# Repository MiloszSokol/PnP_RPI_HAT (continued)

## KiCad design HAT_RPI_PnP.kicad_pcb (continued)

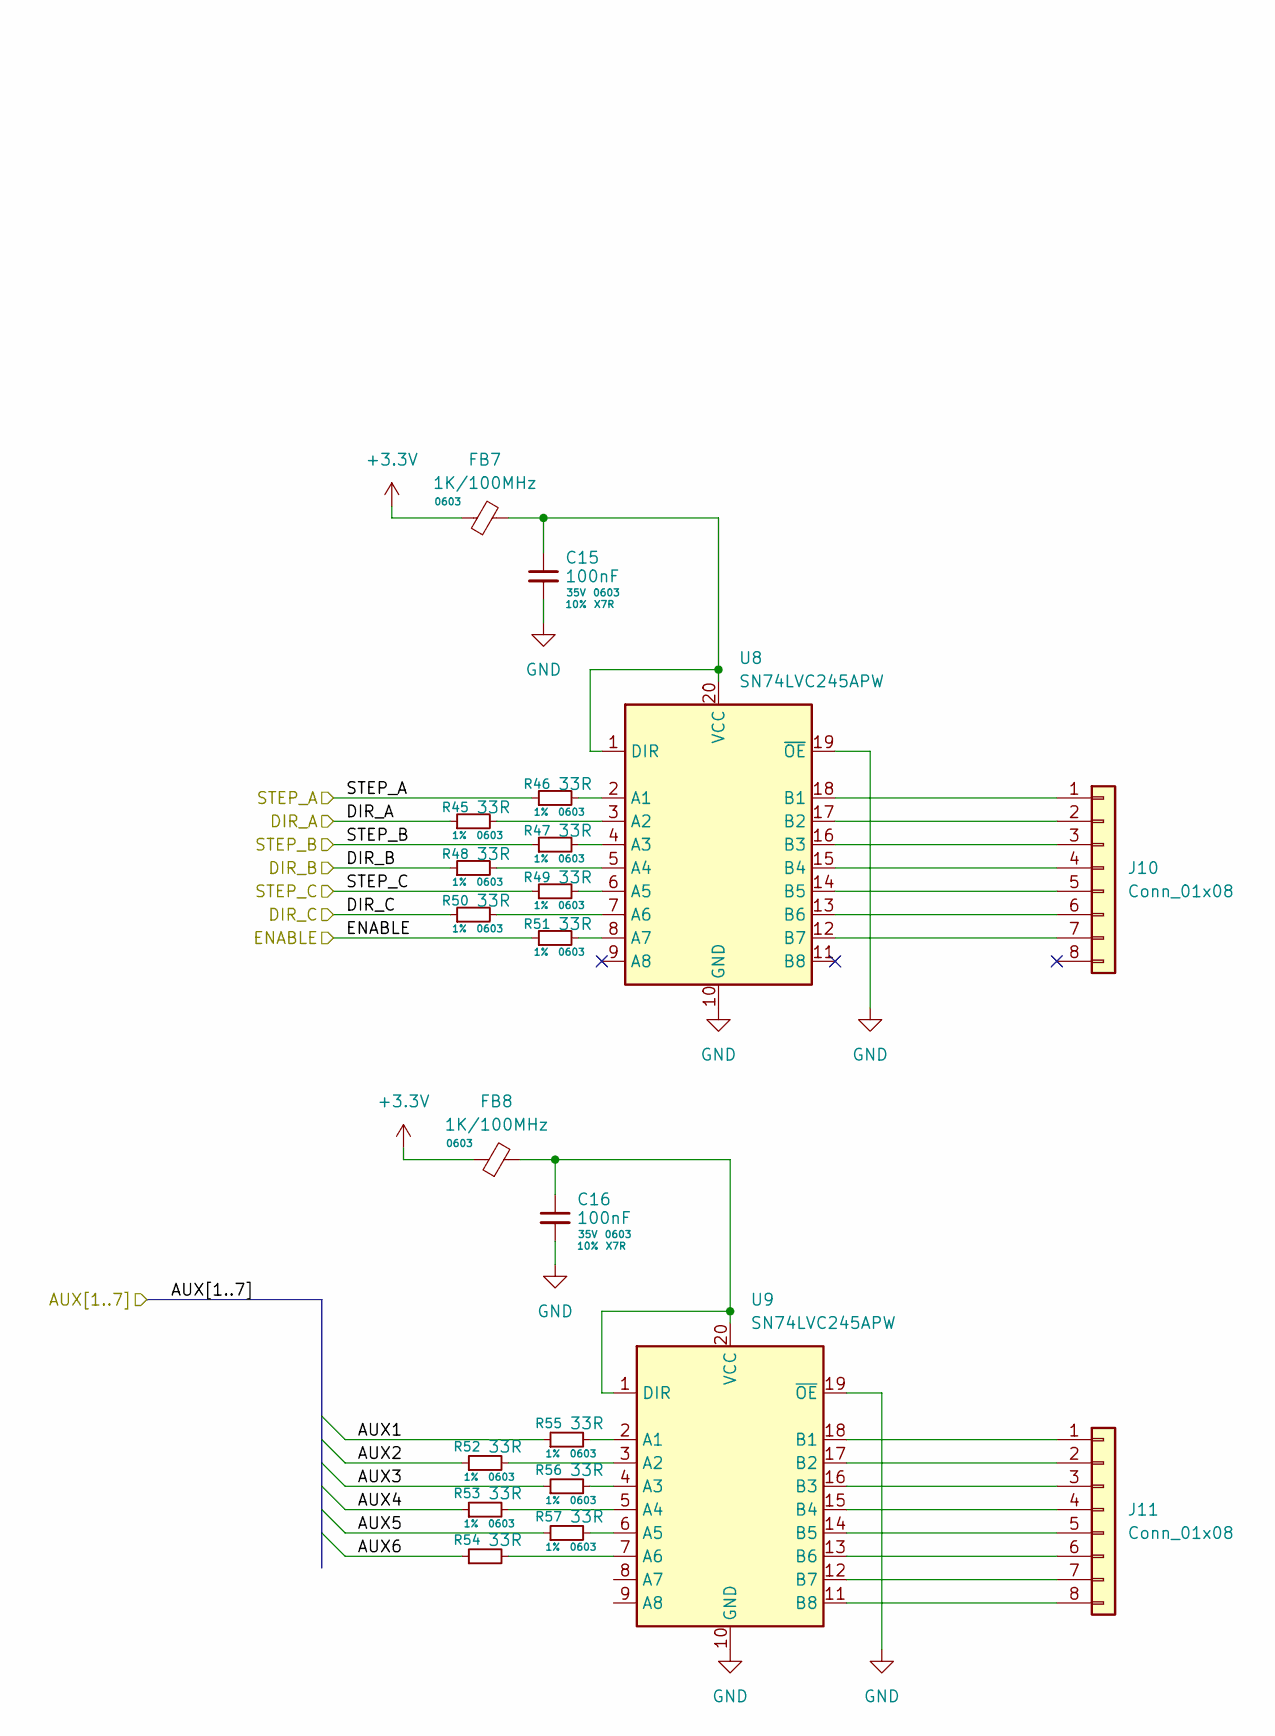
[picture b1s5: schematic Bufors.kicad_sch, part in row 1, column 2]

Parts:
C15, C16: 100nF; C_0603_1608Metric; Tolerance 10%; Voltage 35V
FB7, FB8: 1K/100MHz; L_0603_1608Metric
J10, J11: Conn_01x08; JST_PH_B8B-PH-K_1x08_P2.00mm_Vertical
R45, R46, R47, R48, R49, R50, R51, R52, R53, R54, R55, R56, R57: 33R; R_0603_1608Metric; Tolerance 1%
U8, U9: SN74LVC245APW; TSSOP-20_4.4x6.5mm_P0.65mm

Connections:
+3.3V: FB7.1, FB8.1; also elsewhere on the board
/AUX1: R55.1; also elsewhere on the board
/AUX2: R52.1; also elsewhere on the board
/AUX3: R56.1; also elsewhere on the board
/AUX4: R53.1; also elsewhere on the board
/AUX5: R57.1; also elsewhere on the board
/AUX6: R54.1; also elsewhere on the board
/DIR_A: R45.1; also elsewhere on the board
/DIR_B: R48.1; also elsewhere on the board
/DIR_C: R49.1; also elsewhere on the board
/ENABLE: R51.1; also elsewhere on the board
/STEP_A: R46.1; also elsewhere on the board
/STEP_B: R47.1; also elsewhere on the board
/STEP_C: R50.1; also elsewhere on the board
GND: C15.2, C16.2, U8.10 (GND), U8.19 (~OE), U9.10 (GND), U9.19 (~OE); also elsewhere on the board
unnamed: J10.1, U8.18 (B1)
unnamed: J10.2, U8.17 (B2)
unnamed: J10.3, U8.16 (B3)
unnamed: J10.4, U8.15 (B4)
unnamed: J10.5, U8.14 (B5)
unnamed: J10.6, U8.13 (B6)
unnamed: J10.7, U8.12 (B7)
unnamed: J11.1, U9.18 (B1)
unnamed: J11.2, U9.17 (B2)
unnamed: J11.3, U9.16 (B3)
unnamed: J11.4, U9.15 (B4)
unnamed: J11.5, U9.14 (B5)
unnamed: J11.6, U9.13 (B6)
unnamed: J11.7, U9.12 (B7)
unnamed: J11.8, U9.11 (B8)
unnamed: R46.2, U8.2 (A1)
unnamed: R45.2, U8.3 (A2)
unnamed: R47.2, U8.4 (A3)
unnamed: R48.2, U8.5 (A4)
unnamed: R49.2, U8.6 (A5)
unnamed: R50.2, U8.7 (A6)
unnamed: R51.2, U8.8 (A7)
unnamed: C15.1, FB7.2, U8.1 (DIR), U8.20 (VCC)
unnamed: R55.2, U9.2 (A1)
unnamed: R52.2, U9.3 (A2)
unnamed: R56.2, U9.4 (A3)
unnamed: R53.2, U9.5 (A4)
unnamed: R57.2, U9.6 (A5)
unnamed: R54.2, U9.7 (A6)
unnamed: C16.1, FB8.2, U9.1 (DIR), U9.20 (VCC)

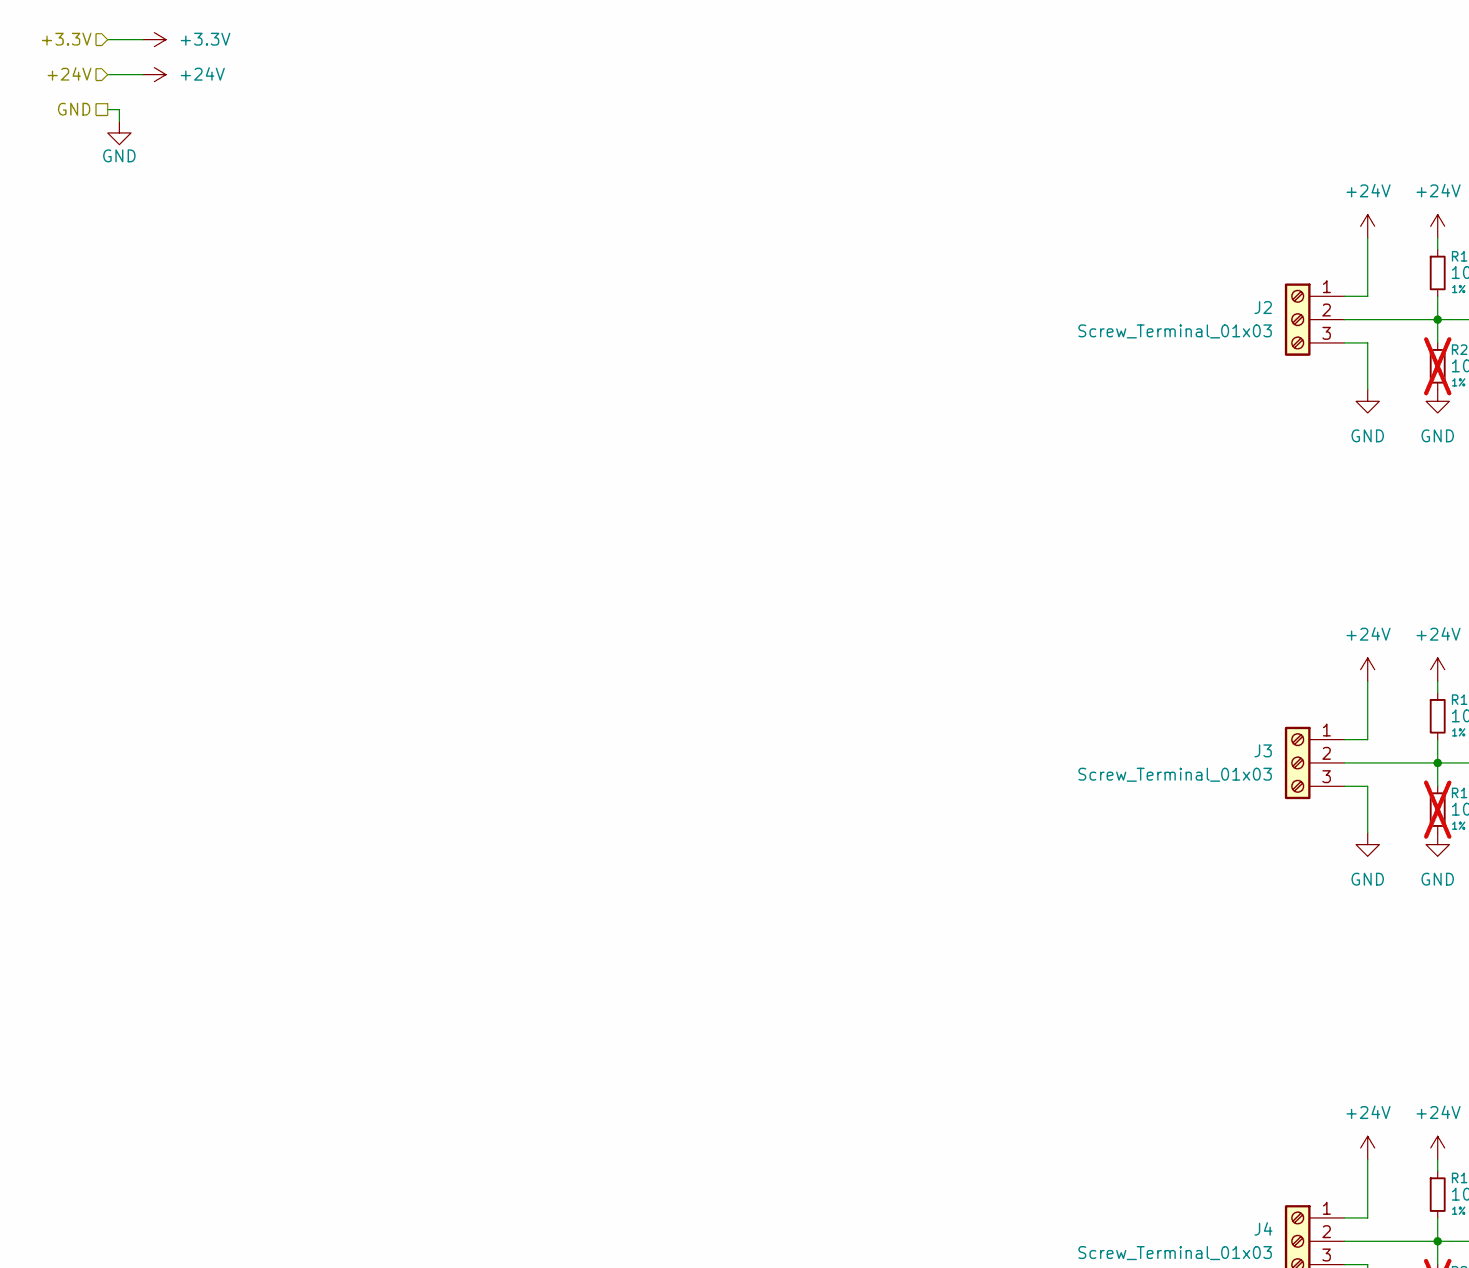
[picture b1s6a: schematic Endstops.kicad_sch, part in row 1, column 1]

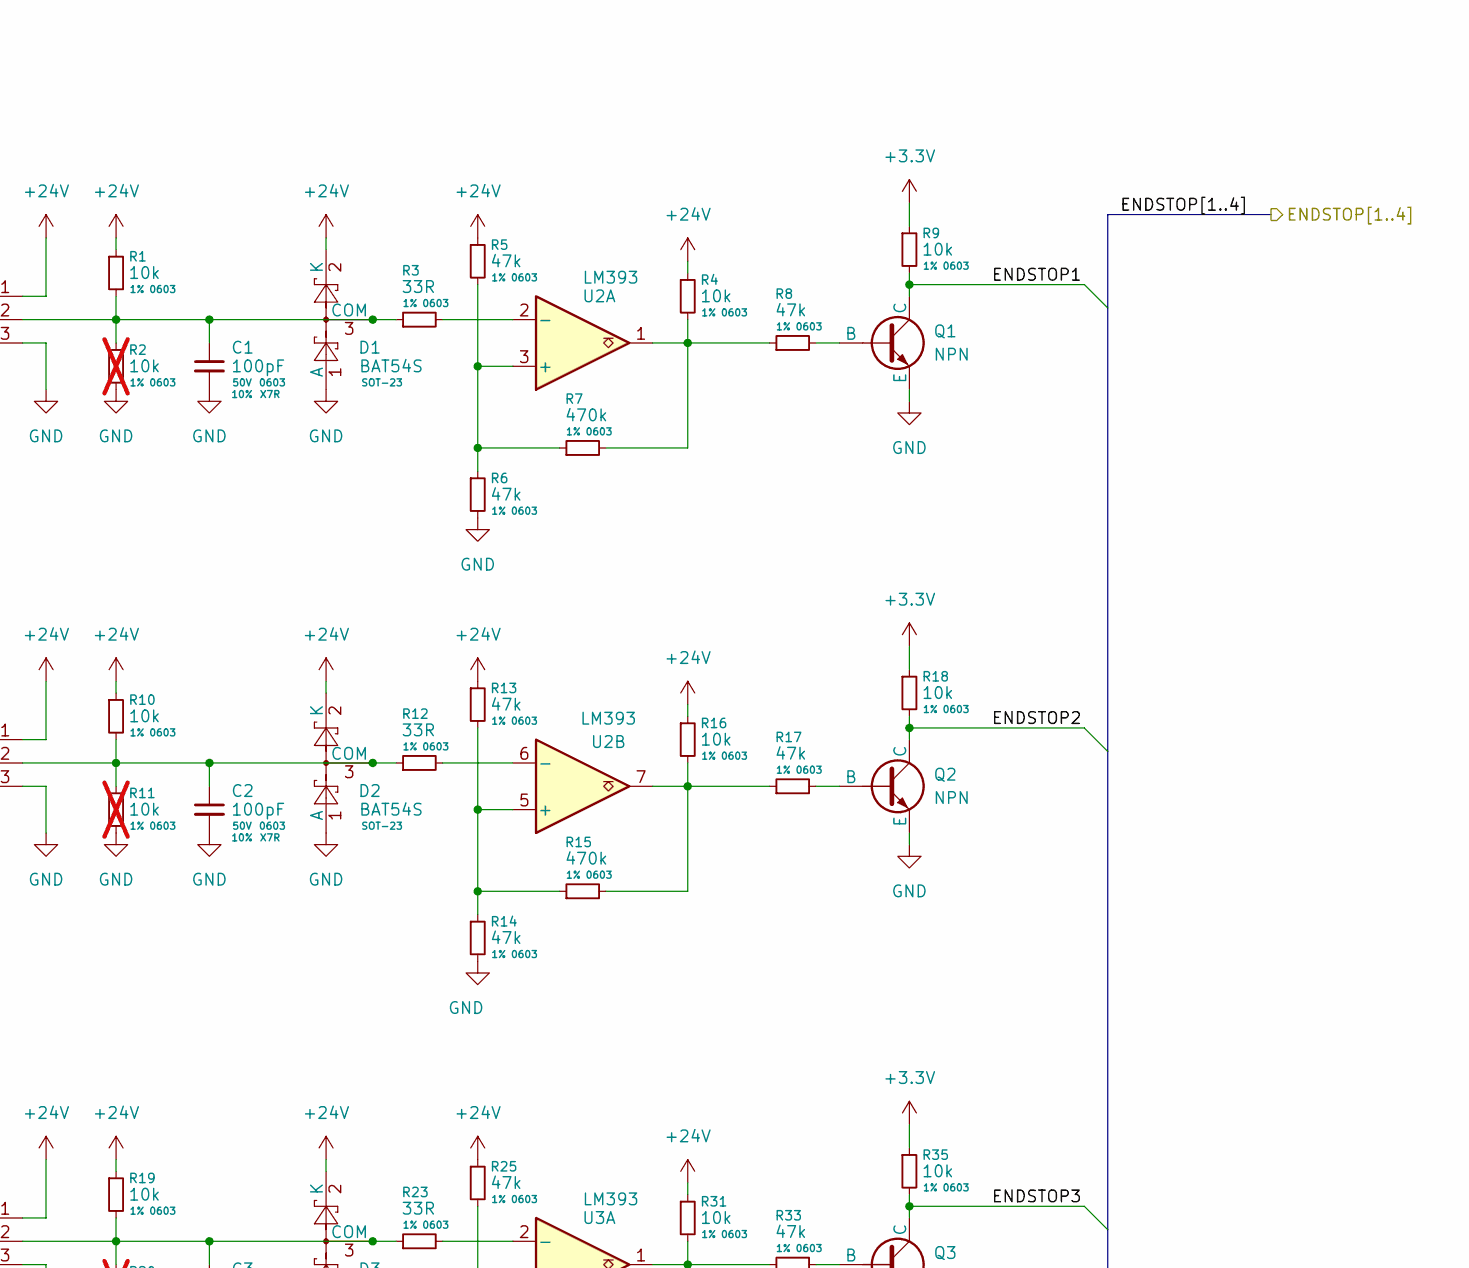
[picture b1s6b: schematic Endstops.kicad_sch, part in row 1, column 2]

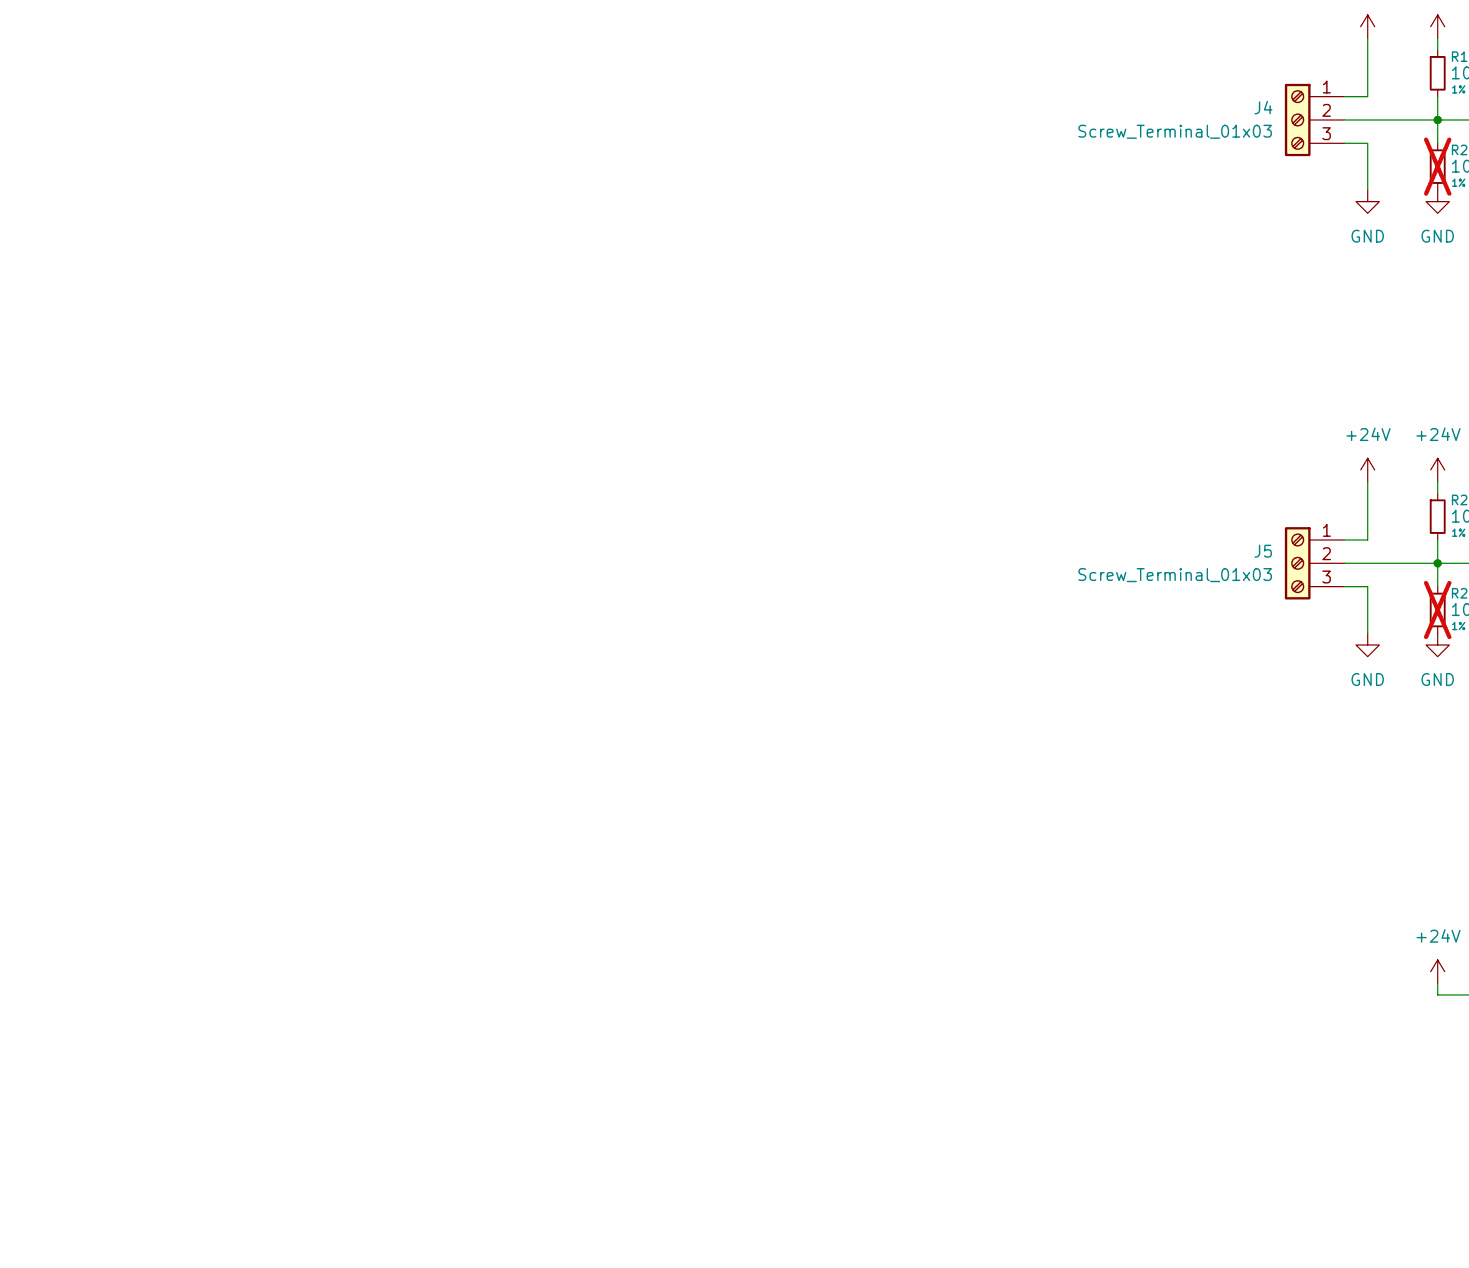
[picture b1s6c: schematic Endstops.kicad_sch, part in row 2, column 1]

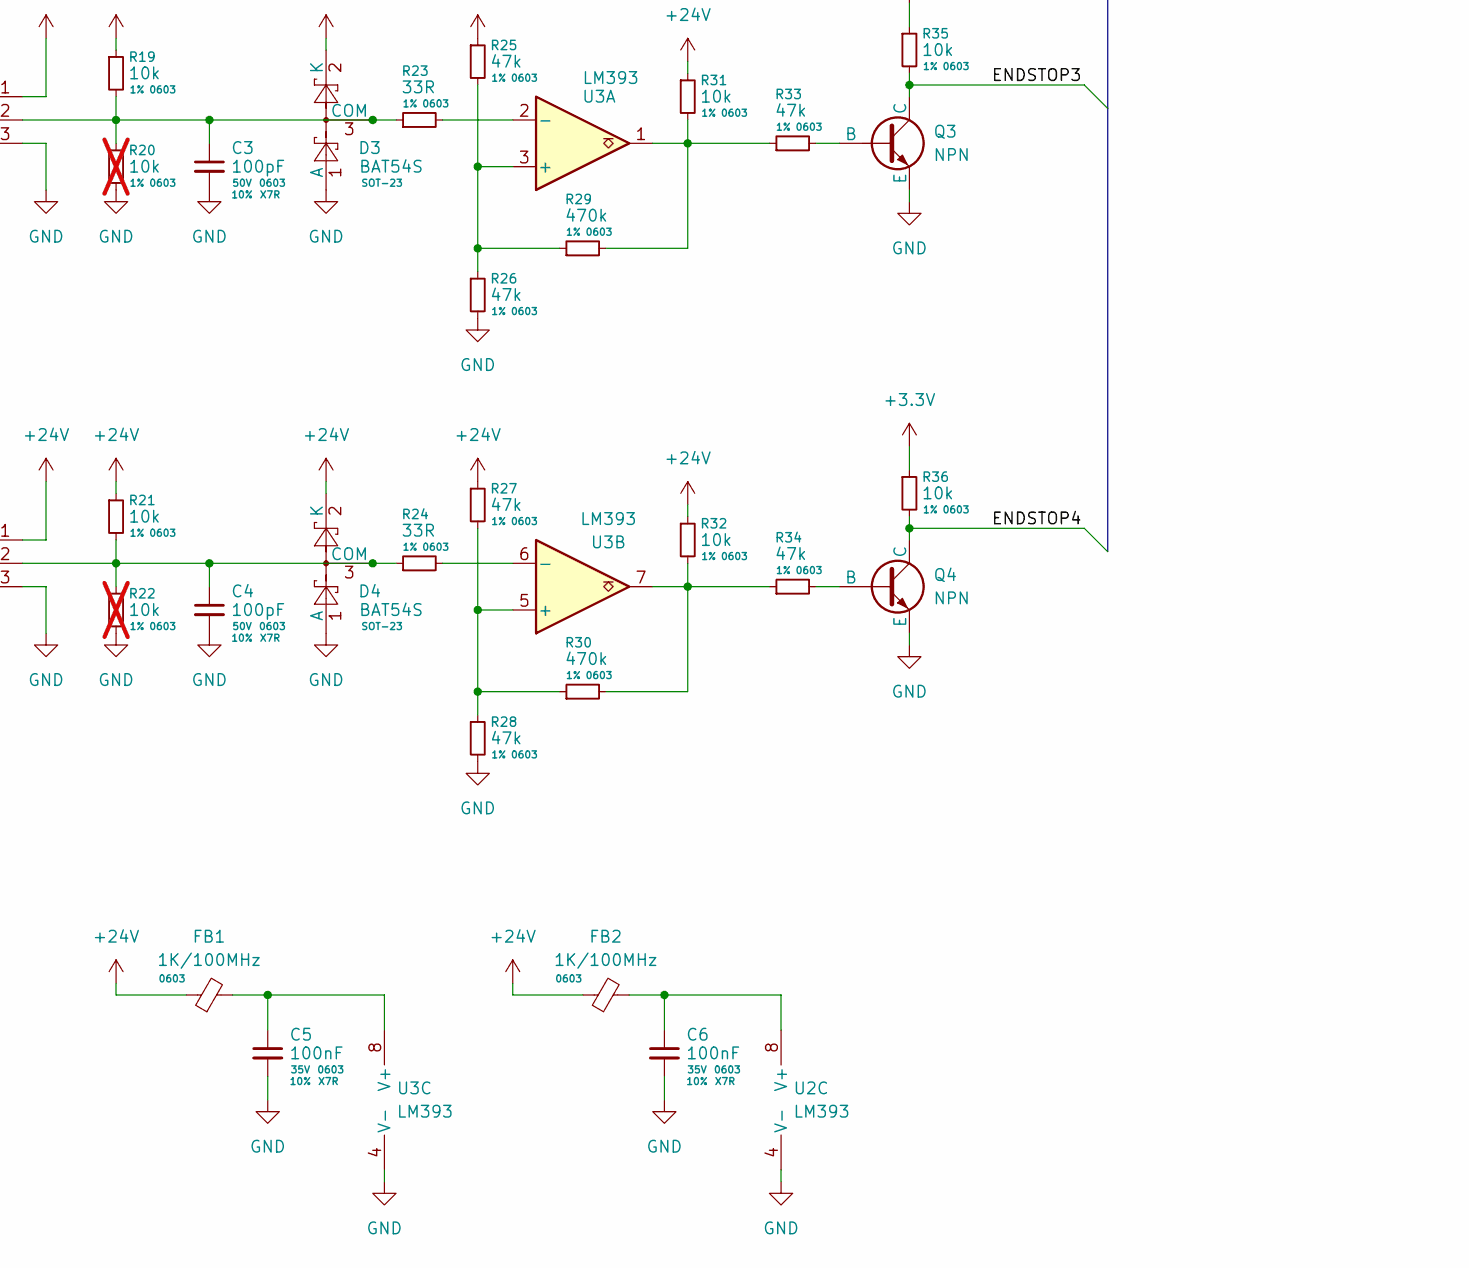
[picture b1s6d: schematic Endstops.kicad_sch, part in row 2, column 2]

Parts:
C1, C2, C3, C4: 100pF; C_0603_1608Metric; Tolerance 10%; Voltage 50V
C5, C6: 100nF; C_0603_1608Metric; Tolerance 10%; Voltage 35V
D1, D2, D3, D4: BAT54S; SOT-23
FB1, FB2: 1K/100MHz; L_0603_1608Metric
J2, J3, J4, J5: Screw_Terminal_01x03; TerminalBlock_4Ucon_1x03_P3.50mm_Horizontal
Q1, Q2, Q3, Q4: NPN; TSOT-23
R1, R4, R9, R10, R16, R18, R19, R21, R31, R32, R35, R36: 10k; R_0603_1608Metric; Tolerance 1%
R2, R11, R20, R22: 10k; R_0603_1608Metric; Tolerance 1%; not fitted
R3, R12, R23, R24: 33R; R_0603_1608Metric; Tolerance 1%
R5, R6, R8, R13, R14, R17, R25, R26, R27, R28, R33, R34: 47k; R_0603_1608Metric; Tolerance 1%
R7, R15, R29, R30: 470k; R_0603_1608Metric; Tolerance 1%
U2, U3: LM393; SOIC-8_5.3x5.3mm_P1.27mm

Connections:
+3.3V: R9.1, R18.1, R35.1, R36.1; also elsewhere on the board
+24V: D1.2 (K), D2.2 (K), D3.2 (K), D4.2 (K), FB1.1, FB2.1, J2.1, J3.1, J4.1, J5.1, R1.1, R4.1, R5.1, R10.1, R13.1, R16.1, R19.1, R21.1, R25.1, R27.1, R31.1, R32.1; also elsewhere on the board
/ENDSTOP1: Q1.1 (C), R9.2; also elsewhere on the board
/ENDSTOP2: Q2.1 (C), R18.2; also elsewhere on the board
/ENDSTOP3: Q3.1 (C), R35.2; also elsewhere on the board
/ENDSTOP4: Q4.1 (C), R36.2; also elsewhere on the board
GND: C1.2, C2.2, C3.2, C4.2, C5.2, C6.2, D1.1 (A), D2.1 (A), D3.1 (A), D4.1 (A), J2.3, J3.3, J4.3, J5.3, Q1.3 (E), Q2.3 (E), Q3.3 (E), Q4.3 (E), R2.2, R6.2, R11.2, R14.2, R20.2, R22.2, R26.2, R28.2, U2.4 (V-), U3.4 (V-); also elsewhere on the board
unnamed: C1.1, D1.3 (COM), J2.2, R1.2, R2.1, R3.1
unnamed: C2.1, D2.3 (COM), J3.2, R10.2, R11.1, R12.1
unnamed: C3.1, D3.3 (COM), J4.2, R19.2, R20.1, R23.1
unnamed: C4.1, D4.3 (COM), J5.2, R21.2, R22.1, R24.1
unnamed: Q1.2 (B), R8.2
unnamed: Q2.2 (B), R17.2
unnamed: Q3.2 (B), R33.2
unnamed: Q4.2 (B), R34.2
unnamed: R4.2, R7.2, R8.1, U2.1
unnamed: R15.2, R16.2, R17.1, U2.7
unnamed: R29.2, R31.2, R33.1, U3.1
unnamed: R30.2, R32.2, R34.1, U3.7
unnamed: R5.2, R6.1, R7.1, U2.3 (+)
unnamed: R3.2, U2.2 (-)
unnamed: R13.2, R14.1, R15.1, U2.5 (+)
unnamed: R12.2, U2.6 (-)
unnamed: C6.1, FB2.2, U2.8 (V+)
unnamed: R25.2, R26.1, R29.1, U3.3 (+)
unnamed: R23.2, U3.2 (-)
unnamed: R27.2, R28.1, R30.1, U3.5 (+)
unnamed: R24.2, U3.6 (-)
unnamed: C5.1, FB1.2, U3.8 (V+)

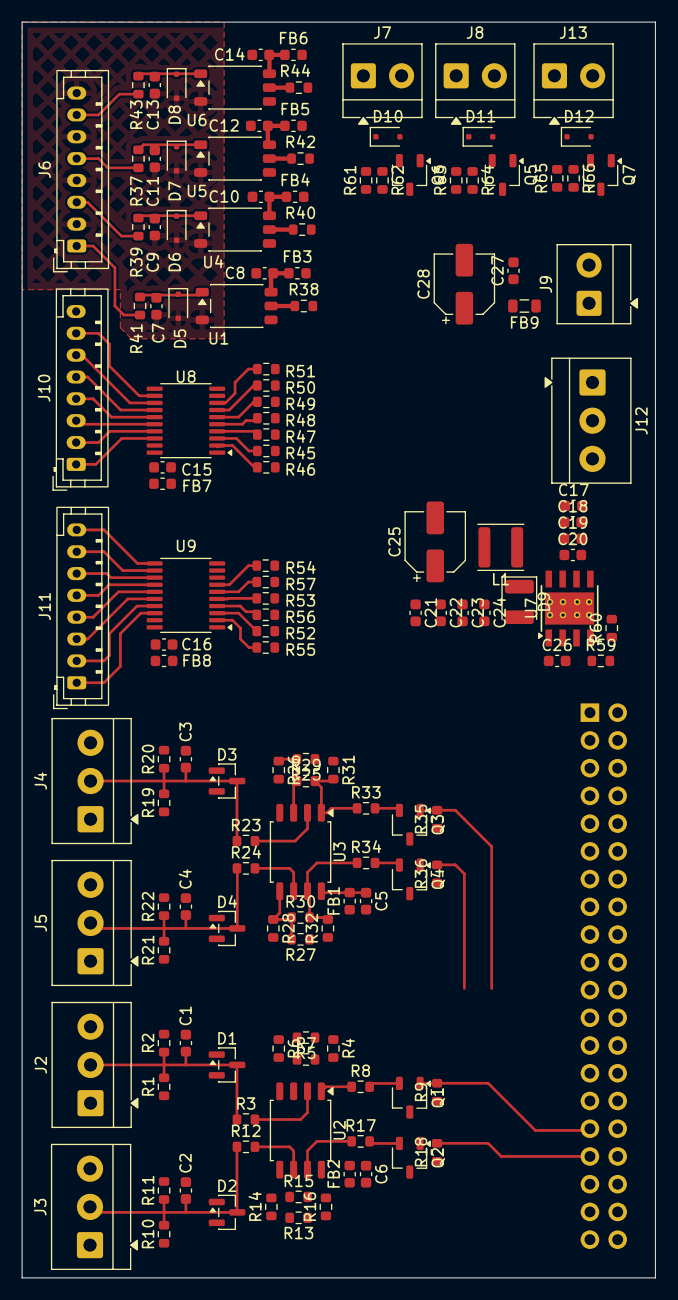
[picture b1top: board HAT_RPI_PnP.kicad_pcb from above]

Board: 2 copper layers, 58.0 x 115.0 mm, 148 parts (1 on the bottom side), 107 nets.

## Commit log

2026-02-25 0.1 sch
2026-03-01 rel 0.1
